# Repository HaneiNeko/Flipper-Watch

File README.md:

# Flipper Watch

WOKWI Simulation Project : https://wokwi.com/projects/414080295914760193

Used librarys : https://github.com/HaneiNeko/Menu-Library-Arduino

## Description
This project is a Flipper Zero like ! <br>
You can capture and put back 433 mHz, Infra Red, RFID and NFC signals. <br>
I used a Arduino Leonardo Micro for microprocessor because he can 
emulate au mouse and a keybord, and he is very small.

For the shematic and the footprint, I used Kicad software.
because it's a free and open source software,
he is very easy to use !

### Images

## Installation
Download the git project <br> 
or use
```sh
git clone https://github.com/HaneiNeko/Flipper-Watch.git
```

## How to use the project
Use the electronic shema for create the PCB <br>
Next, upload the code in the .ino file !

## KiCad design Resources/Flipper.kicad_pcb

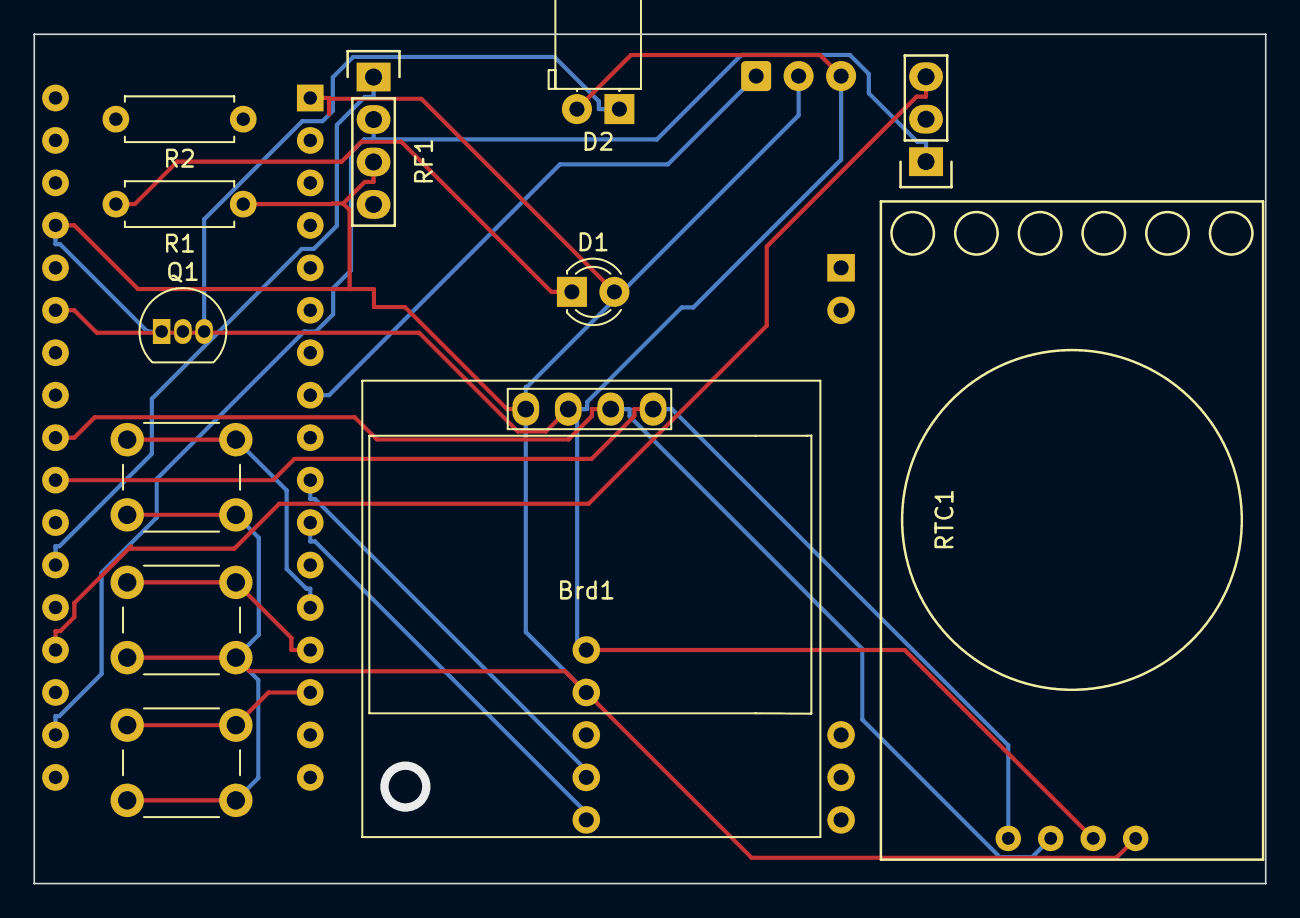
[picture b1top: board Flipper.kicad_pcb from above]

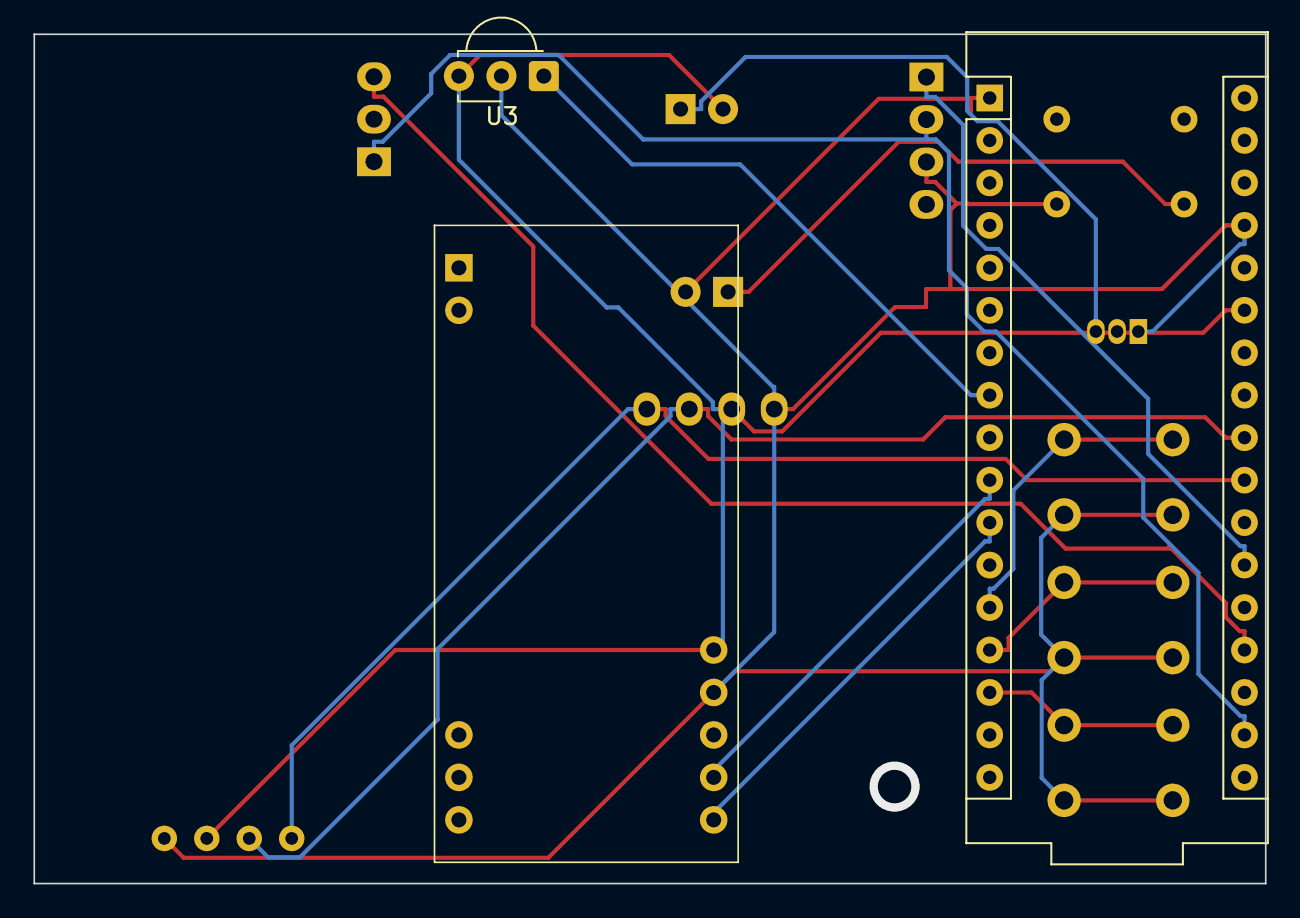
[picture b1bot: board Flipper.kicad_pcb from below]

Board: 2 copper layers, 73.7 x 50.8 mm, 15 parts (3 on the bottom side), 16 nets.

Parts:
Brd1: SSD1306; 128x64OLED
D1: LED; LED_D3.0mm
D2: IR_TRANSMITTER_LED; LED_D5.0mm_Horizontal_O1.27mm_Z3.0mm
Q1: BC547; TO-92_Inline
R1: 220; R_Axial_DIN0207_L6.3mm_D2.5mm_P7.62mm_Horizontal
R2: 470; R_Axial_DIN0207_L6.3mm_D2.5mm_P7.62mm_Horizontal
RF1: RF_Transmitter_433_MHz; RF_Receiver_433_MHz
RF2: RF_Receiver_433_MHz; RF_Transmitter_433_MHz
RTC1: RTC_DS3231
SW1: UP_BUTTON; SW_PUSH_6mm
SW2: SELECT_BUTTON; SW_PUSH_6mm
SW3: DOWN_BUTTON; SW_PUSH_6mm
U1: Arduino_Micro
U2: RDM6300; RDM6300_B38.5x18.2mm
U3: VS1838B; Vishay_MINICAST-3Pin

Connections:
+3.3V: RF1.2 (VCC), RF2.1 (VCC), U1.19 (3V3)
+5V: Brd1.2 (VCC), D2.2 (A), RTC1.2 (VCC), U1.29 (+5V), U2.10 (5V), U3.3 (VSS)
A0: RF2.3 (DATA), U1.21 (A0/D18)
A2: RF1.1 (DATA), U1.23 (A2/D20)
A4: Brd1.4 (SDA), RTC1.4 (SCL), U1.25 (A4/D22)
A5: Brd1.3 (SCL), RTC1.3 (SDA), U1.26 (A5/D23)
D3: U1.8 (~D3/SCL), U3.1 (OUT)
D5: U1.10 (~D5), U2.7 (RX)
D6: U1.11 (~D6/A7), U2.6 (TX)
D8: SW1.1, U1.13 (D8/A8)
D9: SW2.1, U1.14 (~D9/A9)
D10: SW3.1, U1.15 (~D10/A10)
D16: D1.2 (A), U1.1 (D16)
GND: Brd1.1 (GND), Q1.1 (C), R1.1, RF1.3 (GND), RTC1.1 (GND), SW1.2, SW2.2, SW3.2, U1.31 (GND), U2.9 (GND), U3.2 (GND)
unnamed: D1.1 (K), R1.2
unnamed: D2.1 (K), Q1.3 (E)

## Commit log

2024-11-03 Update Readme file
2024-11-03 Add images directory
2024-11-04 Update README file 2
2024-11-04 Update README descruption
2024-11-09 Add simulation link
2024-11-10 Add the code
2024-11-10 Add some badges
2024-11-15 Add resources directory
2024-11-20 Update the shematic
2024-11-21 Add used librarys

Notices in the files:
README.md:
License: CC0
